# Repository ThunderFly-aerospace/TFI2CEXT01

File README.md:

# TFI2CEXT01A - I²C bus extender

I²C bus extension module. This module allows an extension of the usable total length of the I2C bus on the UAV. Most I2C bus instances benefit from having TFI2CEXT positioned midway between master and slave, where its signal amplification is most effective in both directions.

In practice, I2C devices vary in driving capability, and I2C signals are often affected by capacitive load or unwanted signal coupling. TFI2CEXT can effectively isolate bus segments, ensuring devices only see the segment's wiring load up to the TFI2CEXT. Thus, placing TFI2CEXT closer to the "problematic" I²C device is optimal.

## Where to get it?

ThunderFly TFI2CEXT01A counter is commercially available from [ThunderFly s.r.o.](https://www.thunderfly.cz/), write an email to info@thunderfly.cz. Or shop it on [Tindie.](https://www.tindie.com/products/thunderfly/tfi2cext01-pixawk-i2c-bus-extender/)

## Parameters

| Parameter | Value | Description |
|-----------|-------|-------------|
| Data rate | Up to 400 kHz | Limited by used [TCA4307 IC](https://www.ti.com/product/TCA4307) |
| I2C Connector | 2x 4-pin JST-GH | Connected in parallel |
| Operating and storage temperature | -20 - +40°C | Limited by case material |
| Operational input voltage | 3.6 - 5.4V |  |
| Mass | ~2 g | PCB |
| Dimensions | 15x25x6(10.5) | One-sided connectors (With connector on both sides) |
| Weather resistance | IP00 |  |

## Features

  * Input Power status LED indicator
  * Optionally possible to solder pass-through I²C connectors to allow a daisy chain of different sensors
  * Ability to isolate I2C bus segments by disconnecting frozen devices
  * Capability to handle differently the Master and a slave bus sides
  * The extender can perform a device reset in case it seems frozen or unresponsive.
  * READY signal indication of the correct connection of both I2C bus sides.

The two I²C Pixhawk connectors on the bottom and top are connected directly. This feature allows easy nesting with other I²C devices onto existing functional bus cabling.

### Device Reset

The TCA4307 has a stuck bus recovery feature. It disconnects the slave side if SDAOUT or SCLOUT is low for about 40 ms, then generates up to 16 pulses on SCLOUT to reset the bus. The slave side reconnects only after the issue is resolved.

### PCB dimensions

The PCB is designed to be mounted in the slit and fixed by screws on the sides. The supposed screw diameter is metric 3mm e.g. DIN 912 M3 Hexagon socket Head Cap Screws.

## Documentation

The additional documentation is available on the [ThunderFly docs website](https://docs.thunderfly.cz/avionics/TFI2CEXT/). 

### Connection 

Due to the device reset capability of TFI2CEXT01 special attention should be dedicated to the proper connection of the module to the UAV. The connector closer to the LEDS should be connected to the Master (e.g. autopilot). The opposite connector at the far side from LEDs should be connected to I²C slaves, e.g. sensors.

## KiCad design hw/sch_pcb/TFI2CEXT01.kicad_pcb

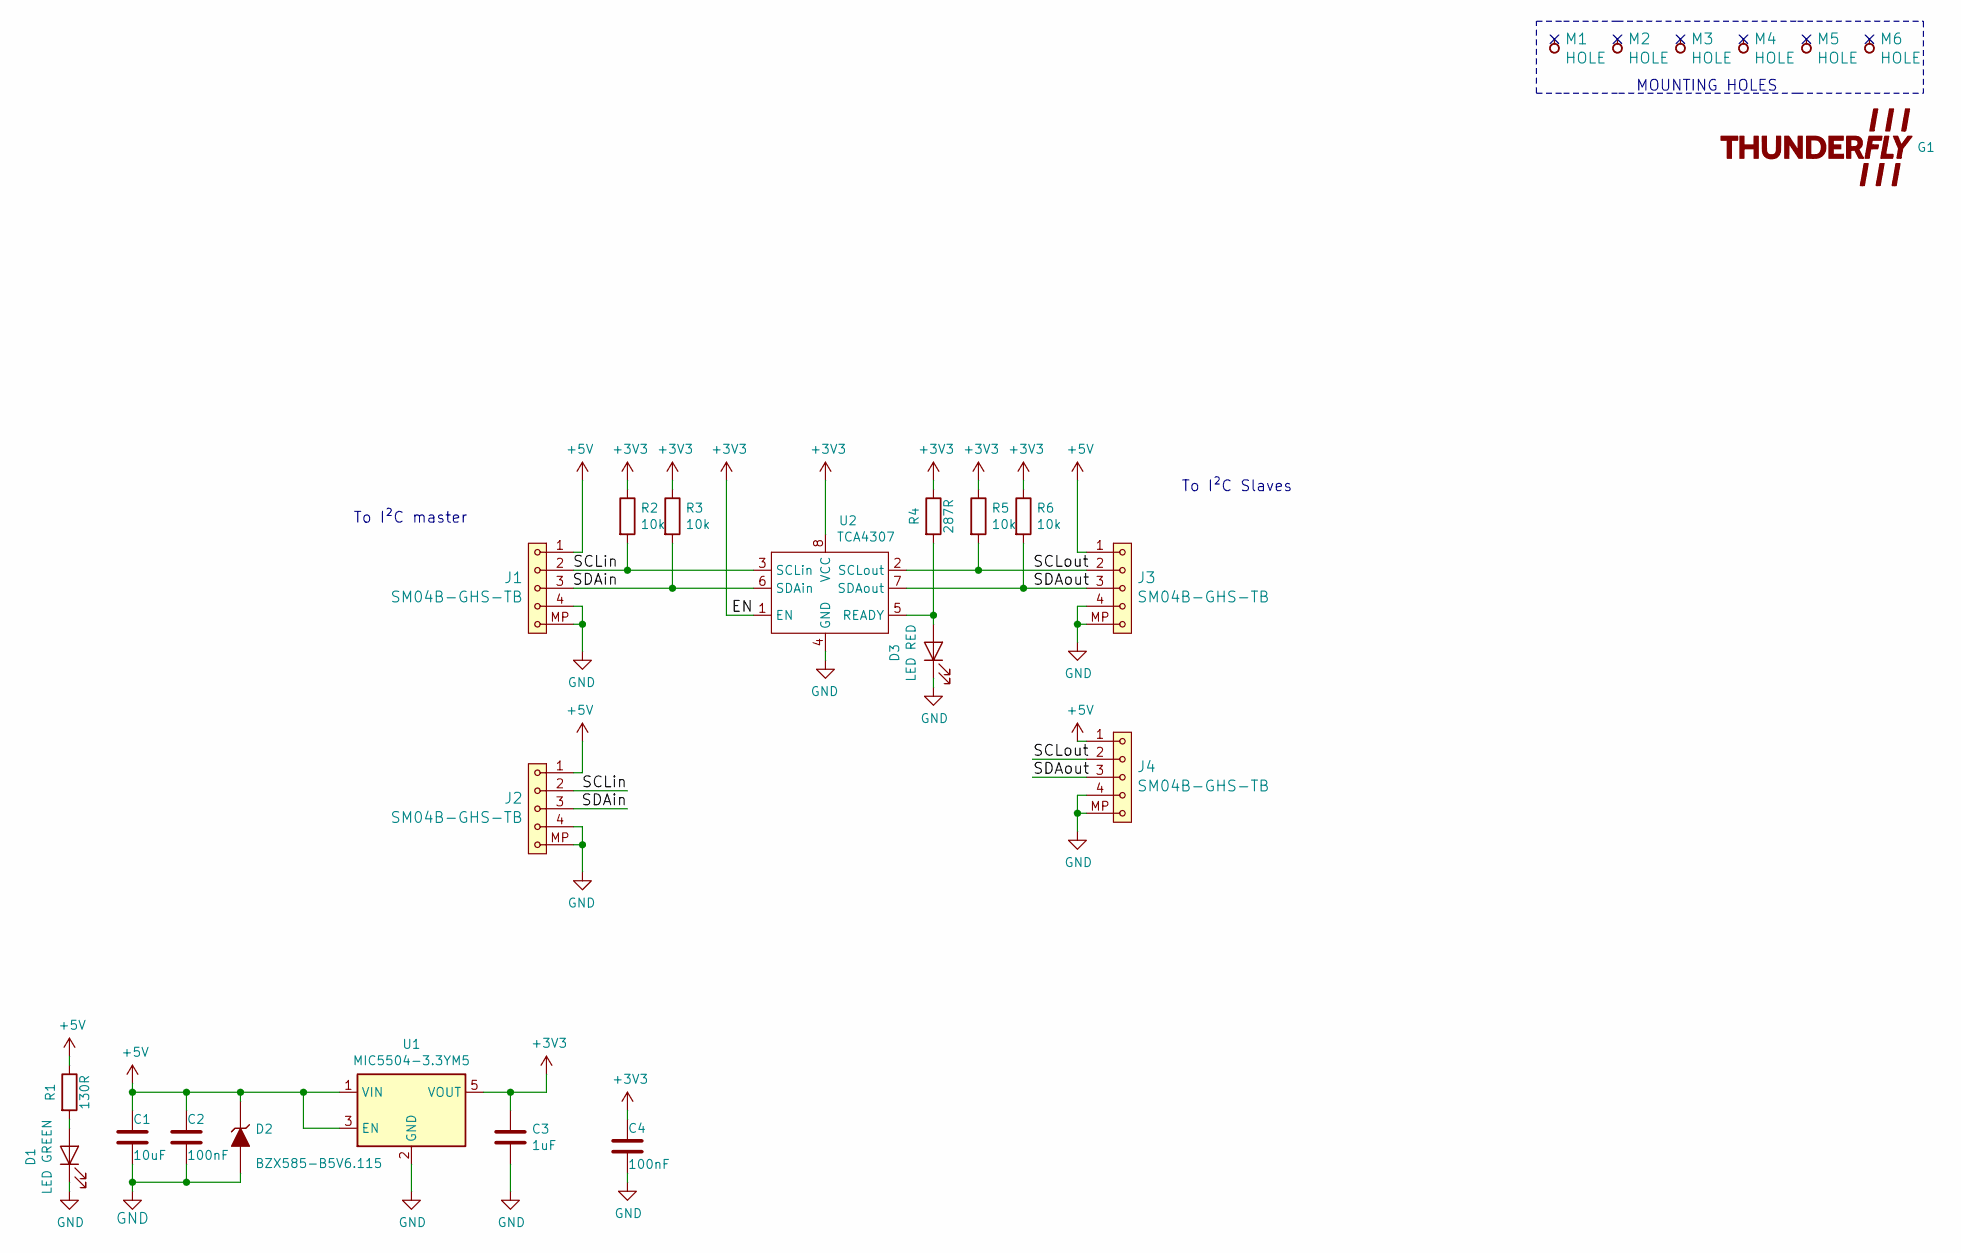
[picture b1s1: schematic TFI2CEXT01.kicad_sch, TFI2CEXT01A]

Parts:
C1: 10uF; C_0805_2012Metric
C2, C4: 100nF; R_0603_1608Metric
C3: 1uF; R_0603_1608Metric
D1: LED GREEN; LED_1206_mill
D2: BZX585-B5V6.115; D_SOD-523
D3: LED RED; LED_1206_mill
G1: LOGO; TF 10x4,7
J1, J2, J3, J4: SM04B-GHS-TB; JST_GH_SM04B-GHS-TB_1x04-1MP_P1.25mm_Horizontal
M1, M2, M3, M4, M5, M6: HOLE; dira_3mm
R1: 130R; R_0603_1608Metric
R2, R3, R5, R6: 10k; R_0603_1608Metric
R4: 287R; R_0603_1608Metric
U1: MIC5504-3.3YM5; SOT-23-5
U2: TCA4307; VSSOP-8_3.0x3.0mm_P0.65mm

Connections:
+3V3: C3.1, C4.1, R2.1, R3.1, R4.1, R5.1, R6.1, U1.5 (VOUT), U2.1 (EN), U2.8 (VCC)
+5V: C1.1, C2.1, D2.1 (K), J1.1, J2.1, J3.1, J4.1, R1.1, U1.1 (VIN), U1.3 (EN)
/SCLin: J1.2, J2.2, R2.2, U2.3 (SCLin)
/SCLout: J3.2, J4.2, R5.2, U2.2 (SCLout)
/SDAin: J1.3, J2.3, R3.2, U2.6 (SDAin)
/SDAout: J3.3, J4.3, R6.2, U2.7 (SDAout)
GND: C1.2, C2.2, C3.2, C4.2, D1.1 (K), D2.2 (A), D3.1 (K), J1.4, J1.MP, J2.4, J2.MP, J3.4, J3.MP, J4.4, J4.MP, U1.2 (GND), U2.4 (GND)
unnamed: D1.2 (A), R1.2
unnamed: D3.2 (A), R4.2, U2.5 (READY)

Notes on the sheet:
To I²C Slaves
To I²C master
MOUNTING HOLES

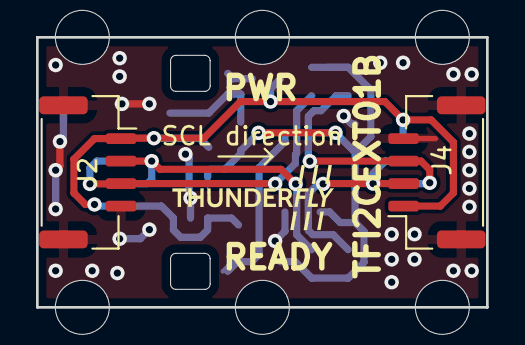
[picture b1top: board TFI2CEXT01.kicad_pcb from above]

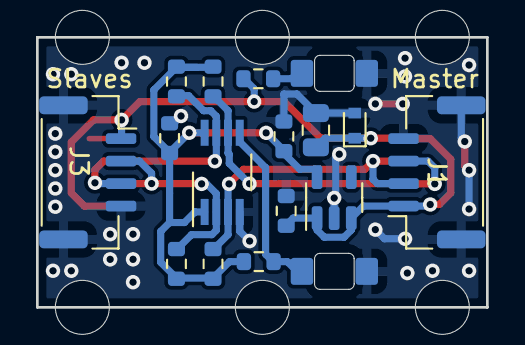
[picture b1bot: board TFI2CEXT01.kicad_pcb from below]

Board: 2 copper layers, 25.0 x 15.0 mm, 26 parts (17 on the bottom side), 9 nets.

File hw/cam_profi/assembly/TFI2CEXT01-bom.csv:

Row,Description,Part,References,Value,Footprint,Quantity Per PCB,Status,Datasheet,UST_id
1,Unpolarized capacitor,C,C2 C4,100nF,R_0603_1608Metric,2, ,,5c70984812875079b91f8bf2
2,Unpolarized capacitor,C,C3,1uF,R_0603_1608Metric,1, ,,5c70984812875079b91f8bc2
3,Unpolarized capacitor,C,C1,10uF,C_0805_2012Metric,1, ,,5c70984812875079b91f8bbd
4,,D_ZENER,D2,BZX585-B5V6.115,D_SOD-523,1, ,,60879d38128750769ee58e48
5,Light emitting diode,LED,D1,LED GREEN,LED_1206_mill,1, ,,5c70984412875079b91f8895
6,Light emitting diode,LED,D3,LED RED,LED_1206_mill,1, ,,5c70984412875079b91f8896
7,1x05 2.54 mm pitch header,SM04B-GHS-TB,J1 J2 J3 J4,SM04B-GHS-TB,JST_GH_SM04B-GHS-TB_1x04-1MP_P1.25mm_Horizontal,4, ,,5c86273d1287500b4e0280be
8,,HOLE,M1 M2 M3 M4 M5 M6,HOLE,dira_3mm,6, ,,
9,Resistor,R,R1,130R,R_0603_1608Metric,1, ,,5cd08b17128750448e4542b1
10,Resistor,R,R4,287R,R_0603_1608Metric,1, ,,651a975c462c6d9e7205504d
11,Resistor,R,R2 R3 R5 R6,10k,R_0603_1608Metric,4, ,,5c70984512875079b91f8962
12,"300mA Low-dropout Voltage Regulator, Vout 3.3V, Vin up to 5.5V, SOT-23",MIC5504-3.3YM5,U1,MIC5504-3.3YM5,SOT-23-5,1, ,http://ww1.microchip.com/downloads/en/DeviceDoc/MIC550X.pdf,5c7255e81287500b4e112ea2
13,,TCA4307,U2,TCA4307,VSSOP-8_3.0x3.0mm_P0.65mm,1, ,https://www.ti.com/lit/ds/symlink/tca4307.pdf?ts=16176074181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,6087a3f3128750769ee58f03





Project info:
Schematic:,TFI2CEXT01
Variant:,default
Revision:,
Date:,2021-04-05
KiCad Version:,7.0.7-7.0.7~ubuntu23.04.1
Statistics:
Component Groups:,13
Component Count:,25
Fitted Components:,25
Number of PCBs:,1
Total Components:,25

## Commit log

2021-05-25 First schematics
2021-05-25 Update title block.
2021-05-25 Edit PCB
2021-05-25 Layout improvement.
2021-05-25 Images
2021-05-25 Add secondary input connector #2.
2021-05-25 Generating production data
2021-05-25 The first layout
2021-05-25 Edit
2021-05-25 Finishing the design
2021-05-25 Update documentation.
2021-05-25 Crop black boarder from the images.
2021-06-06 Improved Slave and Master side marking. #6.
2022-01-14 Add module dimensions
2022-01-27 Fix typo in header
2023-05-27 update actions
2023-05-27 Update workflow files
2023-05-27 rename source files
2023-09-27 Upravy pred vyrobou 01B
2023-09-27 Edit kicad_outputs.yml
2023-09-27 Update actions products
2023-09-27 Add pasta layers
2023-10-02 Edit UST_ID
2023-10-04 Edit B.Fab
2024-07-01 Update README.md
    Fix grammar.
